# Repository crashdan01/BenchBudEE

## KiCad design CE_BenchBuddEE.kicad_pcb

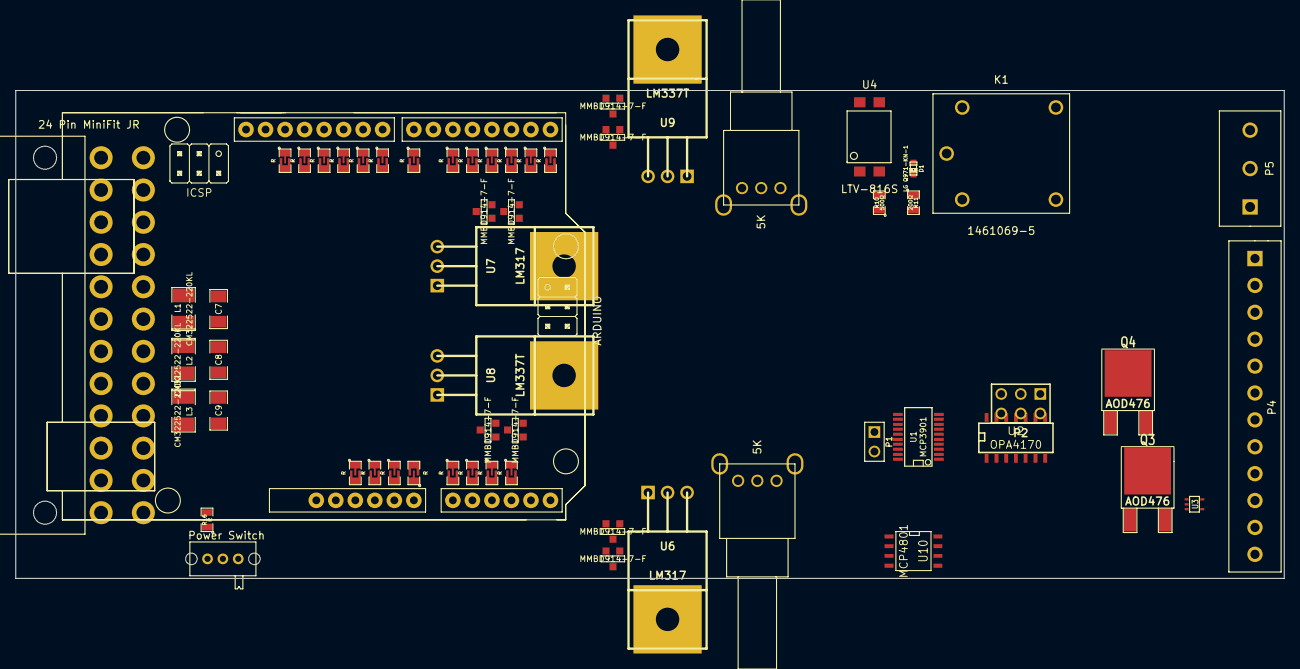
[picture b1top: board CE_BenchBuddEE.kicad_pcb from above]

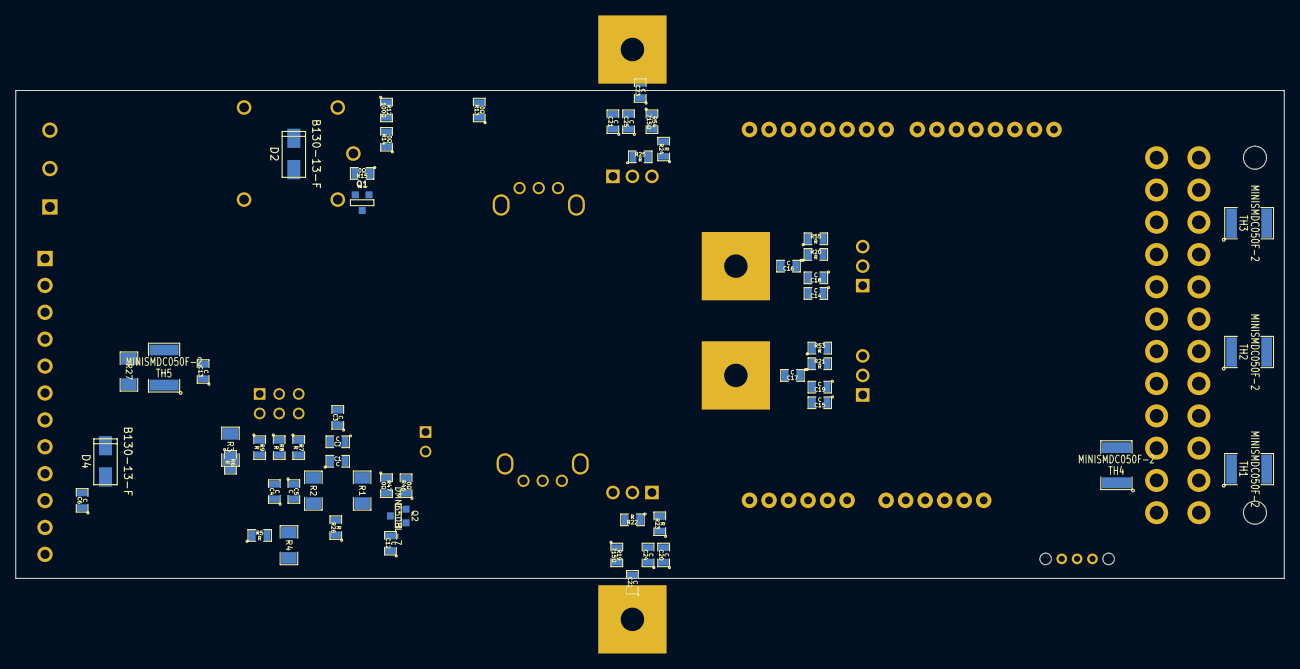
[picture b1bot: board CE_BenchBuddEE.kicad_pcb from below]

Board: 4 copper layers, 165.1 x 63.5 mm, 116 parts (56 on the bottom side), 93 nets, no tracks yet.

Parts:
ARD1: ARDUINO; Arduino_Uno_R3_Footprint
C1, C2, C3, C4, C5, C6, C12, C13, C14, C15, C16, C17, C18, C19, C20, C21, C22, C23, C24, C25: C; SM0805
C7, C8, C9: C; SM1206
D1: LG Q971-KN-1; LED-0603
D2, D4: B130-13-F; SMA
D5, D6, D7, D8, D9, D10, D11, D12: MMBD914-7-F; SOT23-DIODE
K1: 1461069-5; TE-SPDT
L1, L2, L3: CM322522-220KL; SM1210L
P1: CONN_2; PIN_ARRAY_2X1
P2: CONN_3X2; pin_array_3x2
P3: 24 Pin MiniFit JR; ATX_Header
P4: 12 Pin Terminal Block; 12_Pin_TB
P5: 3 Pin TB; 3_Pin_TB
Q1: 2N3904; SOT23EBC
Q2: DMN65D8L-7; SOT23GDS
Q3, Q4: AOD476; DPAK2
R1, R2, R3, R4, R27: R; SM1206
R5, R6, R7, R8, R9, R16, R20, R21, R22, R23, R24, R25, R26, R53, R55: R; SM0805
R10: 500Ω; SM0805
R11: 200Ω; SM0805
R12: 100Ω; SM0805
R13, R14, R15, R46, R47: 0Ω; SM0805
R18, R52: 5K; EVUE3K
R19, R54: 715Ω; SM0805
R28, R29, R30, R31, R32, R33, R34, R35, R36, R37, R38, R39, R40, R41, R42, R43, R44, R48, R49, R50, R51: R; SM0805-BRIDGE
SW1: Power Switch; BB_Switch
TH1, TH2, TH3, TH4, TH5: MINISMDC050F-2; SM1812
U1: MCP3901; SSOP20
U2: OPA4170; SO14E
U3: LMT84; SOT353
U4: LTV-816S; 4-SMD
U6, U7: LM317; TO220
U8, U9: LM337T; TO220
U10: MCP4801; SO8N

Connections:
+3.3V: P4.1, R16.2
+5P: L1.1, TH2.2
+5V: C1.2, C2.1, C6.1, C7.1, C12.2, L1.2, P4.2, R28.1, U1.2, U1.3, U3.4, U10.1
+12C: C13.1, P3.10, TH3.1, TH5.1
+12P: L2.1, R13.1, R14.1, R29.1, TH3.2
+12V: C5.2, C8.1, C14.1, C20.1, D5.2, D9.2, L2.2, U2.4, U6.1, U7.1
-12P: L3.1, TH4.2
-12V: C4.2, C9.2, C15.1, C21.1, D6.1, D10.1, L3.2, U2.11, U8.2, U9.2
/Arduino/CURR_MEAS: Q3.2, Q4.3, R27.1, R32.1, U2.13
/Arduino/FAN_MODE: Q3.1, R44.2
/Arduino/FAN_PWM: Q2.G, R37.2
/Arduino/MISO: R35.2, U1.19
/Arduino/MOSI: R36.2, U1.20, U10.4
/Arduino/RELAY+: R43.2, U4.1
/Arduino/SCLK: R34.2, U1.18, U10.3
/Arduino/V+_ADJ_MON: R22.1, R23.2, R30.1
/Arduino/V-_ADJ_MON: R24.1, R25.2, R31.1
/Arduino/~ADC_CS: R39.2, U1.17
/Arduino/~DR: R42.2, U1.14
/Arduino/~LDAC: R50.2, U10.6
/Arduino/~RESET: R41.2, U1.1
/Fan Driver/FAN_OUT+: D4.2, P4.8, TH5.2
/Fan Driver/FAN_OUT-: D4.1, P4.9, Q4.2
/Fan Driver/TACH_IN: P4.10, R33.1
/Fan Driver/~CS: R40.2, U10.2
/Fan Driver/~LDAC: R51.2, U10.5
/Power Adjustment Monitor/V+_ADJ: C24.1, D9.1, D11.2, P4.4, R19.2, R22.2, U6.3
/Power Adjustment Monitor/V-_ADJ: C25.1, D10.2, D12.1, P4.5, R25.1, R54.2, U9.3
/Relay/RELAY_COM: K1.1, P5.3
/Relay/RELAY_NO: K1.3, P5.2
/Terminal Block/RELAY_COM: K1.4, P5.1
/Thermocouple/CH0+: C3.1, R1.1, U1.4, U2.1
/Thermocouple/CH0-: C3.2, R47.2, U1.5
/Thermocouple/CH1+: U1.7, U3.3
/Thermocouple/CH1-: R46.2, U1.6
/Thermocouple/TC_IN +: P4.11, U2.5
/Thermocouple/TC_IN -: P4.12, U2.10
AGND: C1.1, C2.2, C4.1, C5.1, C6.2, C12.1, C13.2, C14.2, C15.2, C16.2, C17.2, C18.2, C19.2, C20.2, C21.2, C22.2, C23.2, C24.2, C25.2, Q2.S, Q3.3, R2.1, R18.2, R23.1, R24.2, R27.2, R46.1, R47.1, R52.2, R53.1, R55.1, U1.8, U1.11, U3.1, U3.2, U3.5, U10.7
FE_V+: C18.1, D5.1, D7.2, R20.2, U7.3
FE_V-: C19.1, D6.2, D8.1, R21.1, U8.3
GND: C7.2, C8.2, C9.1, P3.5, P4.3, R11.2, R15.1, R48.1, R49.1, SW1.3
unnamed: ARD1.15, R42.1
unnamed: ARD1.16, R41.1
unnamed: ARD1.4, R29.2
unnamed: ARD1.1, R28.2
unnamed: ARD1.2, R48.2
unnamed: ARD1.3, R49.2
unnamed: ARD1.13, R51.1
unnamed: ARD1.14, R50.1
unnamed: ARD1.21, R37.1
unnamed: ARD1.12, R43.1
unnamed: ARD1.8, R33.2
unnamed: ARD1.7, R32.2
unnamed: ARD1.6, R31.2
unnamed: ARD1.5, R30.2
unnamed: ARD1.19, R39.1
unnamed: ARD1.20, R38.1
unnamed: ARD1.11, R44.1
unnamed: ARD1.23, R35.1
unnamed: ARD1.18, R40.1
unnamed: ARD1.22, R36.1
unnamed: ARD1.24, R34.1
unnamed: P1.1, U1.12
unnamed: P1.2, U1.13
unnamed: R1.2, R3.1, U2.2
unnamed: R2.2, R4.1, U2.3
unnamed: R3.2, R5.1, U2.7
unnamed: R4.2, R6.2, U2.8
unnamed: P2.1, P2.3, P2.5, R5.2, U2.6
unnamed: P2.4, R8.1
unnamed: P2.6, R7.1
unnamed: P2.2, R9.1
unnamed: R6.1, R7.2, R8.2, R9.2, U2.9
unnamed: D2.1, K1.5, Q1.3
unnamed: D2.2, K1.2, R14.2
unnamed: R10.2, U4.2
unnamed: R13.2, U4.4
unnamed: D1.1, R12.1, U4.3
unnamed: Q1.2, R12.2
unnamed: D1.2, R11.1
unnamed: Q1.1, R15.2
unnamed: P3.4, P3.6, TH2.1
unnamed: P3.1, P3.2, TH1.1
unnamed: R16.1, SW1.1
unnamed: P3.14, TH4.1
unnamed: P3.16, SW1.2
unnamed: R26.1, U10.8
unnamed: Q4.1, U2.14
unnamed: Q2.D, R26.2, U2.12
unnamed: C16.1, D7.1, R20.1, R55.2, U7.2
unnamed: C17.1, D8.2, R21.2, R53.2, U8.1
unnamed: C22.1, D11.1, R18.1, R19.1, U6.2
unnamed: C23.1, D12.2, R52.1, R54.1, U9.1

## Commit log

2014-01-31 Created initial blanks for schematic and PCB layout
2014-01-31 Added block diagram skeleton and signal pins.
    Added the following hierarchical sheets:
    Arduino
    Power
    Fan Driver
    LED Driver
    Thermocouple
2014-02-04 Blocked out the thermocouple worksheet
    Added the instrumentation amplifier, ADC placeholder and general
    temperature sensor placeholder.
2014-02-05 Added Relay and Fan subsystem block diagrams
2014-02-06 Blocked out the LED Driver and Power sheets
2014-02-06 Completed Arduino Block Diagram and Fan Redesign
    The commits as of this are now up to date with the videos released for
    Contextual Electronics, Week 3.
2014-02-21 Initial layout of relay and thermocouple
    All block diagrams completed through Week 3. Component selection
    spreadsheets created: Bench Buddy Session 1CE.xlsx = official part
    selection and bom.xlsx is the version I came up with.
    Part association and initial layout of the Relay and Thermocouple
    sections completed.
2014-02-22 Initial layout of Arduino and Fan-Current
2014-02-23 Reorganization of power conditioning module
2014-02-23 Association and layout of the power regulator mod
